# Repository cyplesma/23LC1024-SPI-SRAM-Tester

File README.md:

# 23LC1024 SPI SRAM Tester

An Arduino Uno R3 bench tester for 23LC1024 serial SRAM chips. The sketches check SPI communication, write and verify the full 128 KiB address space, and support repeated test passes. The KiCad design is a three-socket test board for extending the single-chip bench setup.

## Project status

| Item | Status |
| --- | --- |
| Single-chip test on Arduino Uno R3 | Full-memory verification passed at 125 kHz, 1 MHz, 4 MHz, and 8 MHz |
| Repeated testing at 8 MHz | 37 passes observed without a reported error |
| Three-socket KiCad board | PCB layout with a bottom ground plane. Operation with all three sockets populated is pending verification. |

## Repository layout

| Path | Contents |
| --- | --- |
| `README.md` | Project overview, test procedure, and bench results |
| `hardware/` | KiCad project (`.kicad_pro`), schematic (`.kicad_sch`), PCB layout (`.kicad_pcb`), and any project-specific libraries |
| `firmware/` | Arduino sketches, each in a folder with the same name as its main `.ino` file |
| `docs/` | Optional schematic PDF, board photos, and Serial Monitor logs |

## Firmware

| Sketch | Purpose |
| --- | --- |
| 96-byte diagnostic | Exercises three access methods over a small memory range and checks the mode register |
| Full-memory test | Writes and verifies 131,072 bytes in 32-byte blocks using `0x00`, `0xFF`, `0x55`, `0xAA`, and an address-derived pattern |
| Continuous SPI clock test | Generates ongoing SPI activity for probing the clock signal |

## Running a test

1. Start with one SRAM chip. Check the chip orientation, power, common ground, and SPI connections. Use the KiCad schematic for board wiring and confirm that the sketch's chip-select setting matches the socket under test.
2. Open the 96-byte diagnostic in the Arduino IDE, select **Arduino Uno** and the correct serial port, and upload it. Set Serial Monitor to the baud rate in the sketch's `Serial.begin()` call.
3. Start with the bench diagnostic settings of SPI mode 3, 125 kHz, and a 5 µs chip-select delay. The bench diagnostic reported `0x40` for sequential mode and passed all three access checks.
4. Upload the full-memory sketch and verify that all five patterns pass. Repeat at higher clock rates if needed, recording the board revision, socket, SPI clock, and pass count for each run.

The memory tests overwrite the addresses they exercise.

## Bench notes

- The first diagnostic read `0x00` from the mode register. Reseating the chip restored the expected `0x40` reading.
- Intermittent data mismatches stopped after the oscilloscope ground clip was removed and the Uno and SRAM common ground was confirmed.
- The single-chip bench results came from jumper-wire testing. The PCB still needs its own run with all three sockets populated.

<!-- Maintainer checklist
- Keep the KiCad project, schematic, PCB layout, and referenced custom libraries together under hardware/.
- Use project-relative paths for any custom libraries and check that the project opens from a fresh clone.
- Put each actual .ino file in its own matching sketch folder under firmware/.
- Add photos or serial logs under docs/ and link them here if desired.
- Update the three-socket status after testing each socket with all three chips populated.
- Add the license files you choose for the hardware and firmware before publishing.
-->

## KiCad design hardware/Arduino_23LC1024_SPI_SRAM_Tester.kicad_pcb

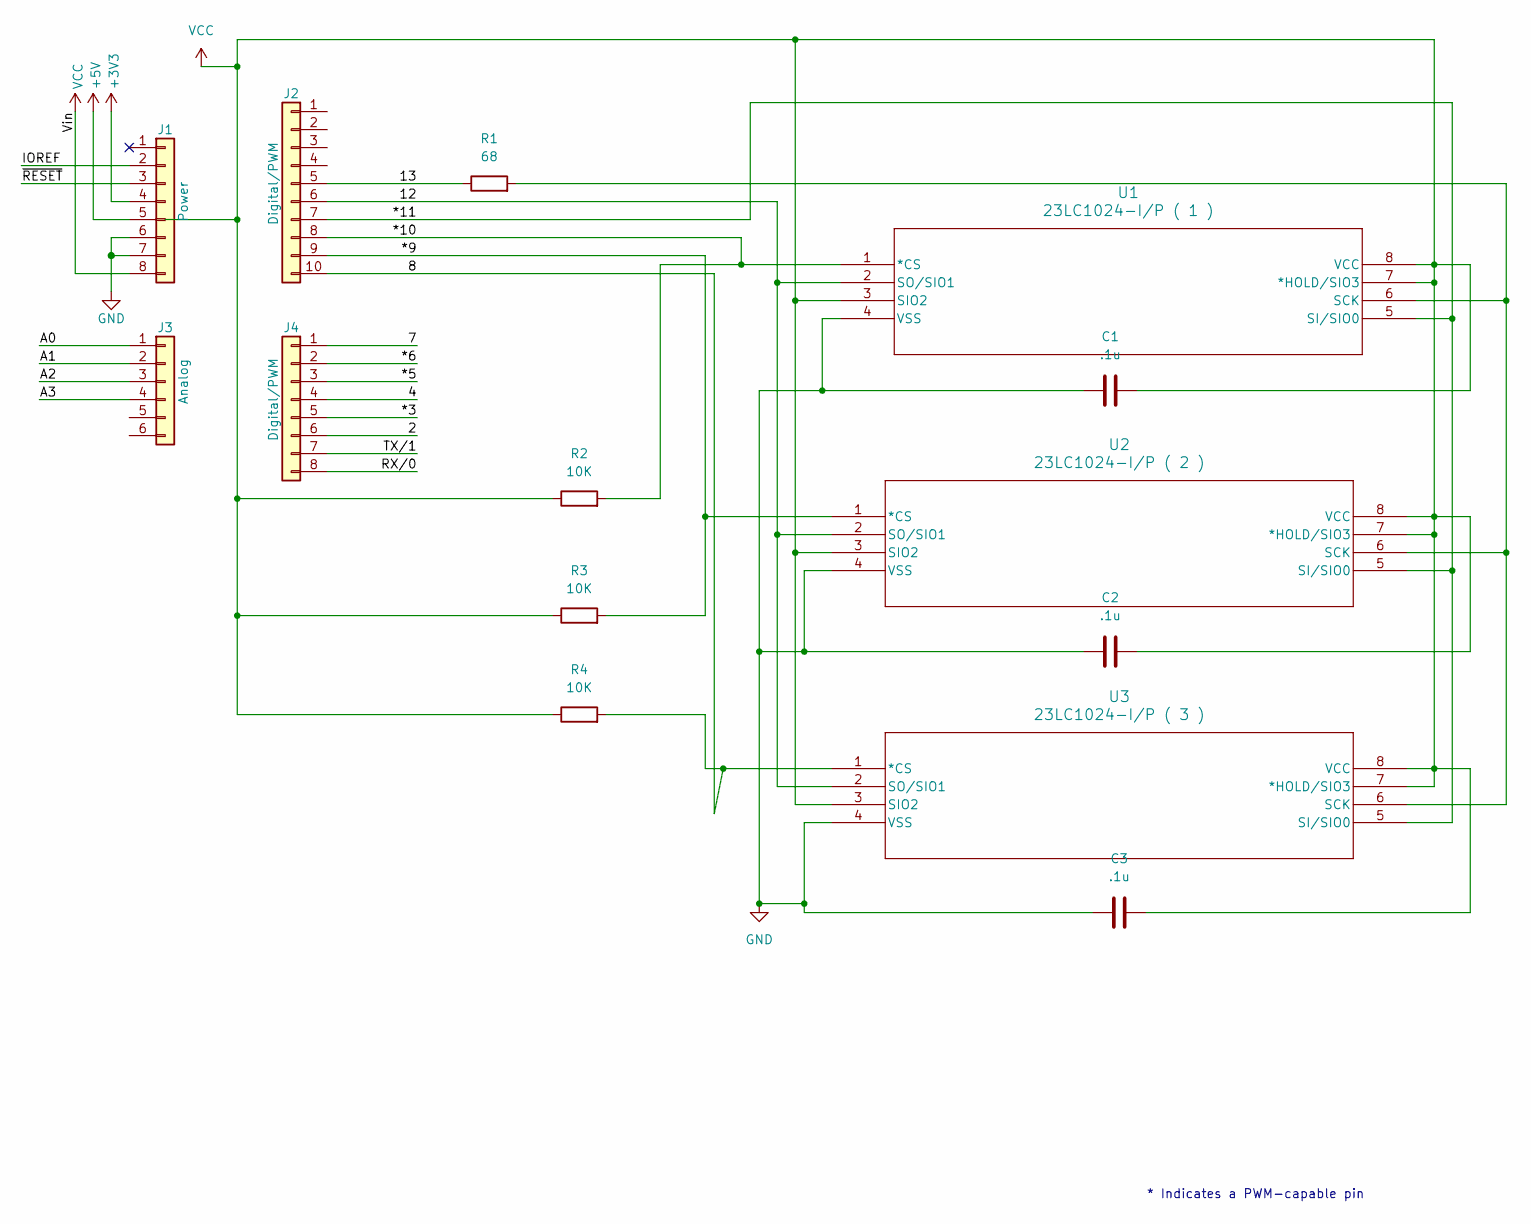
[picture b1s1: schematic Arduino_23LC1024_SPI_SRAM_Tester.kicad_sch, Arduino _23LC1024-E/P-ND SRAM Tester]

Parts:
C1, C2, C3: .1u; C_Disc_D10.0mm_W2.5mm_P5.00mm
J1: Power; PinSocket_1x08_P2.54mm_Vertical
J2: Digital/PWM; PinSocket_1x10_P2.54mm_Vertical
J3: Analog; PinSocket_1x06_P2.54mm_Vertical
J4: Digital/PWM; PinSocket_1x08_P2.54mm_Vertical
R1: 68; R_Axial_DIN0204_L3.6mm_D1.6mm_P5.08mm_Vertical
R2, R3, R4: 10K; R_Axial_DIN0204_L3.6mm_D1.6mm_P5.08mm_Vertical
U1: 23LC1024-I/P ( 1 ); DIP-8_W7.62mm
U2: 23LC1024-I/P ( 2 ); DIP-8_W7.62mm
U3: 23LC1024-I/P ( 3 ); DIP-8_W7.62mm

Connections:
+3V3: J1.4
+5V: J1.5
/2: J4.6
/4: J4.4
/7: J4.1
/8: J2.10, R4.2, U3.1 (*CS)
/12: J2.6, U1.2 (SO/SIO1), U2.2 (SO/SIO1), U3.2 (SO/SIO1)
/13: J2.5, R1.1
/*3: J4.5
/*5: J4.3
/*6: J4.2
/*9: J2.9, R3.2, U2.1 (*CS)
/*10: J2.8, R2.2, U1.1 (*CS)
/*11: J2.7, U1.5 (SI/SIO0), U2.5 (SI/SIO0), U3.5 (SI/SIO0)
/A0: J3.1
/A1: J3.2
/A2: J3.3
/A3: J3.4
/IOREF: J1.2
/RX/0: J4.8
/TX/1: J4.7
/~RESET: J1.3
GND: C1.1, C2.1, C3.1, J1.6, J1.7, U1.4 (VSS), U2.4 (VSS), U3.4 (VSS)
unnamed: R1.2, U1.6 (SCK), U2.6 (SCK), U3.6 (SCK)
VCC: C1.2, C2.2, C3.2, J1.8, R2.1, R3.1, R4.1, U1.3 (SIO2), U1.7 (*HOLD/SIO3), U1.8 (VCC), U2.3 (SIO2), U2.7 (*HOLD/SIO3), U2.8 (VCC), U3.3 (SIO2), U3.7 (*HOLD/SIO3), U3.8 (VCC)

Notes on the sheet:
* Indicates a PWM-capable pin

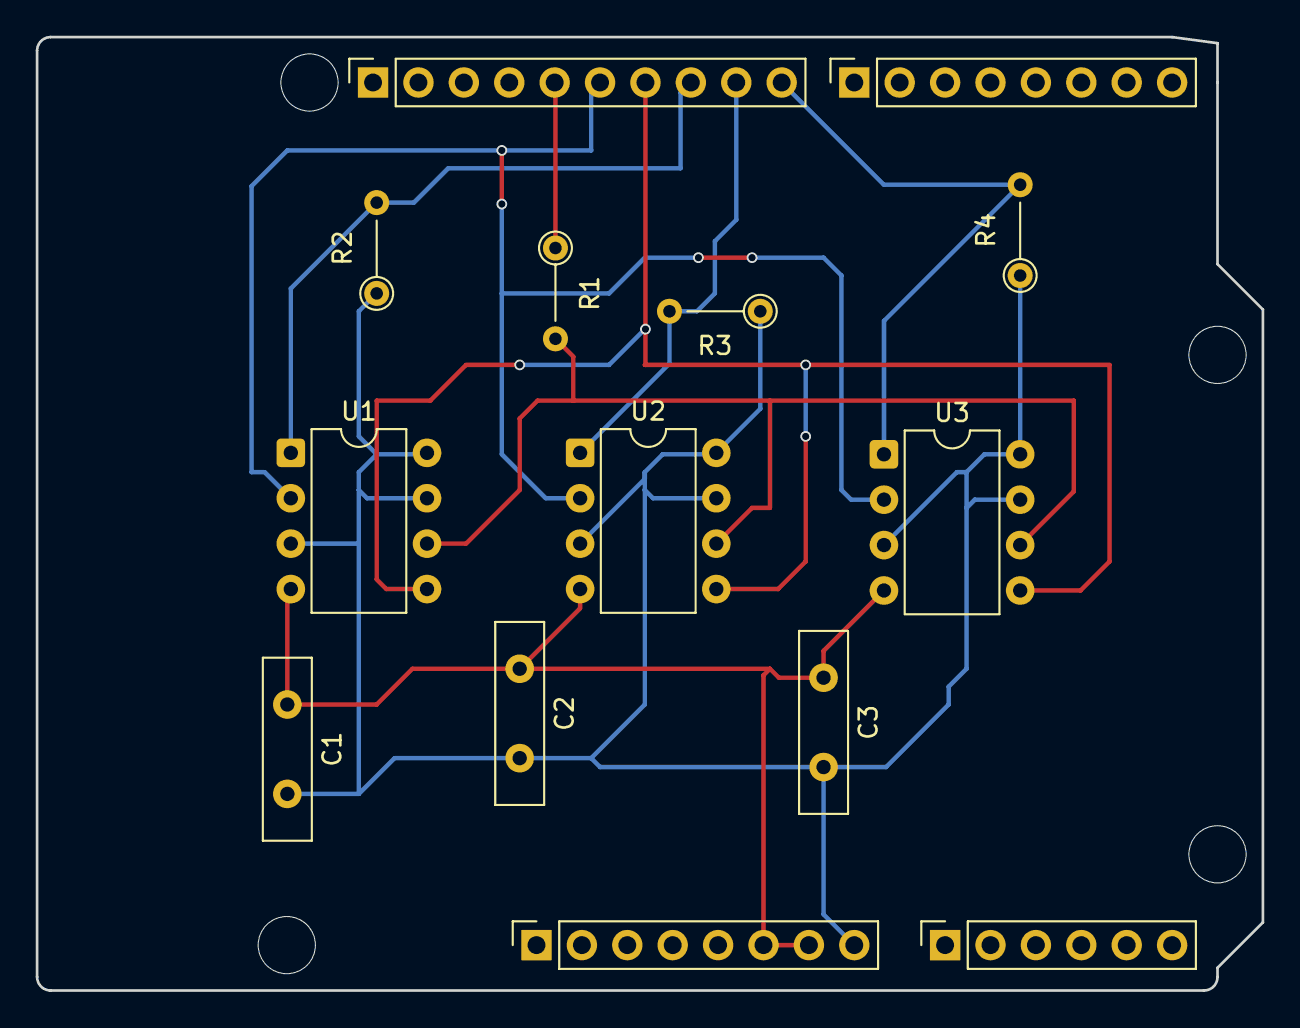
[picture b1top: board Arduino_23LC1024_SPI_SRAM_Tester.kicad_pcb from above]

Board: 2 copper layers, 68.6 x 53.3 mm, 18 parts (0 on the bottom side), 9 nets.

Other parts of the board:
MH1, MH2, MH3, MH4: MountingHole_3.2mm
